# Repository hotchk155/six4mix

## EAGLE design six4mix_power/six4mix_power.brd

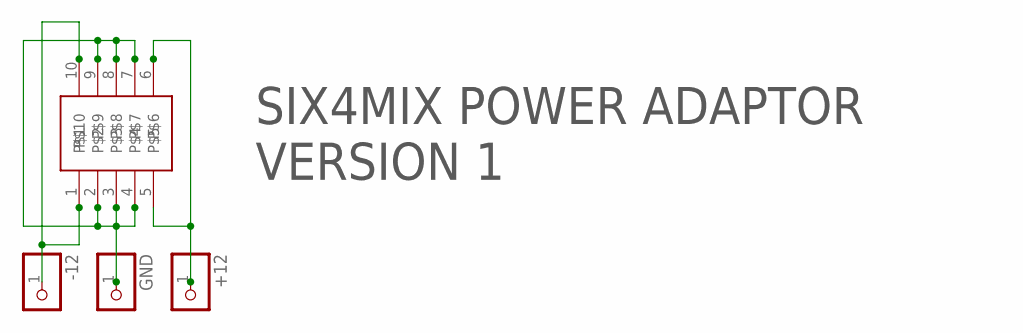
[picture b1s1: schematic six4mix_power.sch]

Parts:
+12: PINHD-1X1; 1X01
-12: PINHD-1X1; 1X01
GND: PINHD-1X1; 1X01
U$1: 2X5SMT

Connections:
GND: GND.1, U$1.2, U$1.3, U$1.4, U$1.7, U$1.8, U$1.9
unnamed: -12.1, U$1.1, U$1.10
unnamed: +12.1, U$1.5, U$1.6

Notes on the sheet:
SIX4MIX POWER ADAPTOR VERSION 1

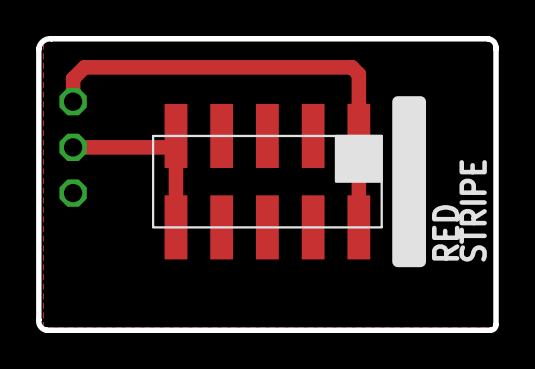
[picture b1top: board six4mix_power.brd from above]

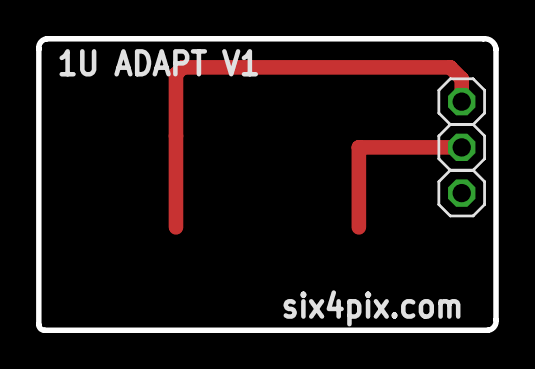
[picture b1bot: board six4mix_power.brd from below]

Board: 2 copper layers, 25.4 x 16.2 mm, 4 parts (3 on the bottom side), 3 nets.

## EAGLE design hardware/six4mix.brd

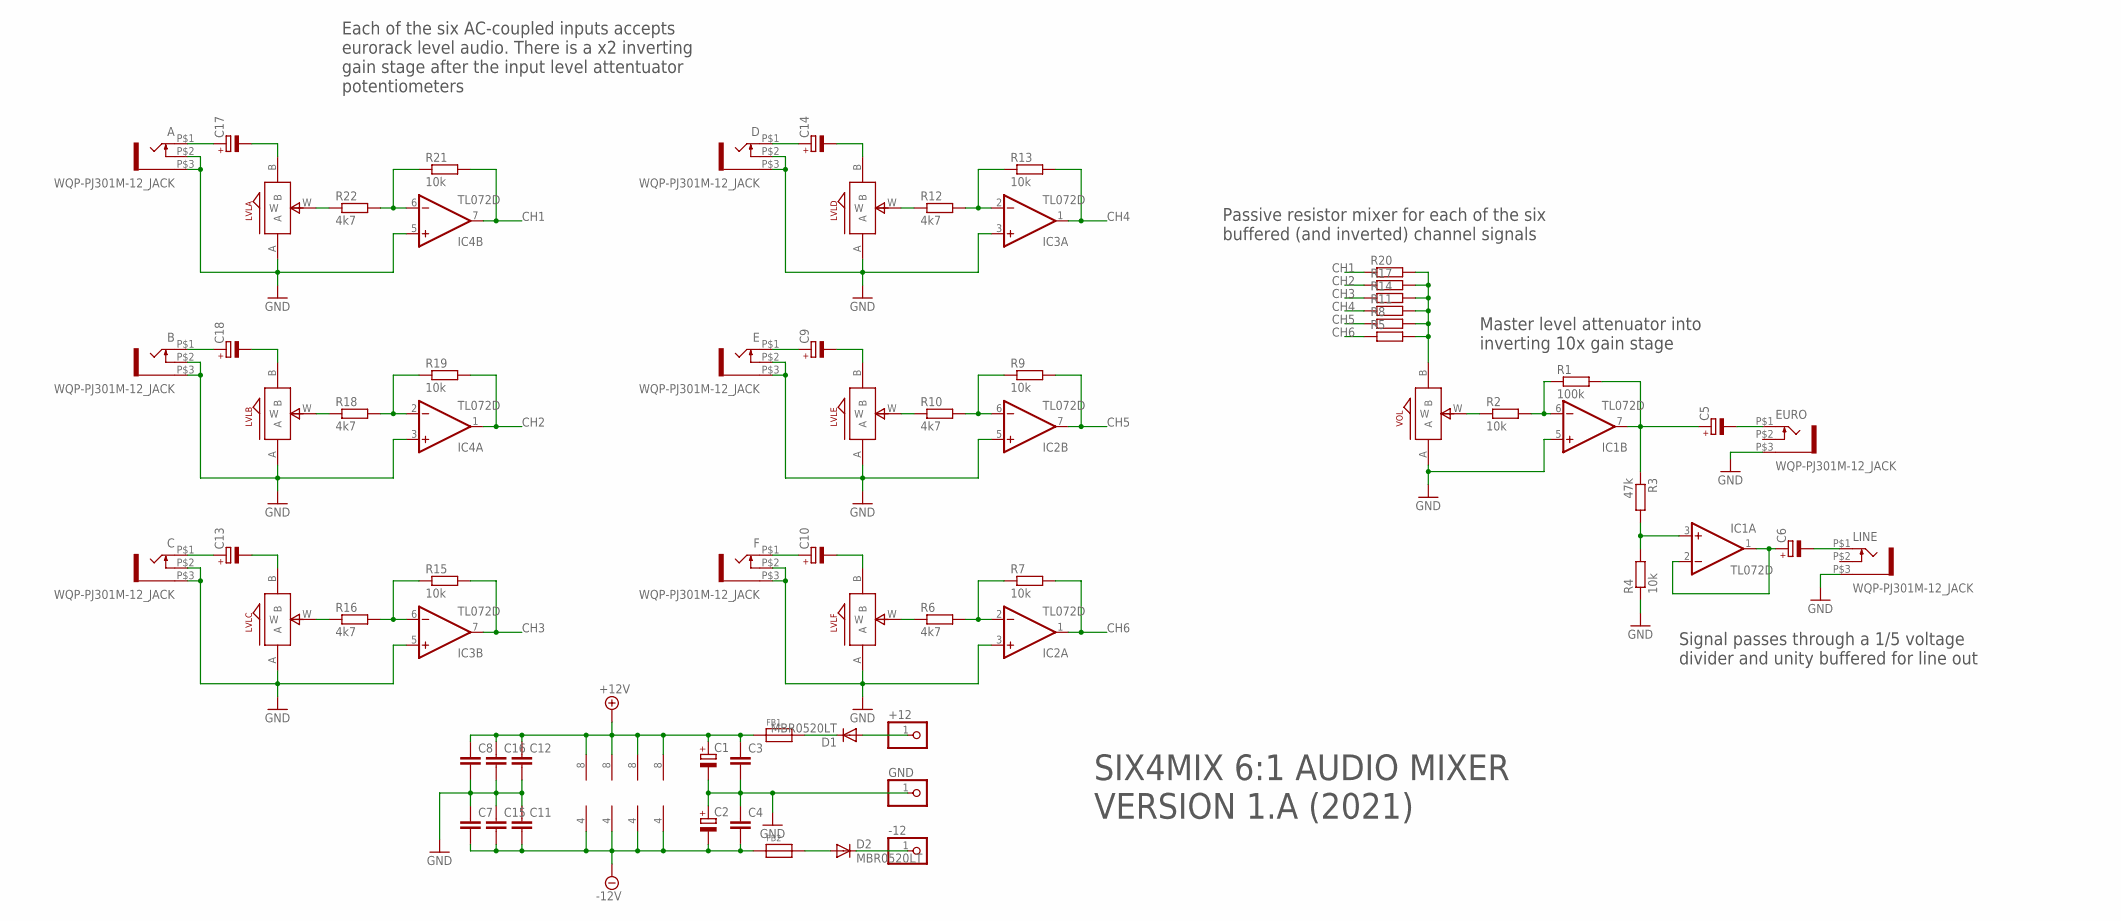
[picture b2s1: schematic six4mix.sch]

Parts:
+12: PINHD-1X1; 1X01
-12: PINHD-1X1; 1X01
A: WQP-PJ301M-12_JACK
B: WQP-PJ301M-12_JACK
C: WQP-PJ301M-12_JACK
C1, C2, C5, C6, C9, C10, C13, C14, C17, C18: CPOL-EUE2-4; E2-4
C3, C4, C7, C8, C11, C12, C15, C16: C-EUC0805; C0805
D: WQP-PJ301M-12_JACK
D1, D2: MBR0520LT; SOD123
E: WQP-PJ301M-12_JACK
EURO: WQP-PJ301M-12_JACK
F: WQP-PJ301M-12_JACK
FB1, FB2: FERRITE; 0603
GND: PINHD-1X1; 1X01
IC1, IC2, IC3, IC4: TL072D; SO08
LINE: WQP-PJ301M-12_JACK
LVLA: ALPS_POT_SMALL; SMALL_ALPS_POT
LVLB: ALPS_POT_SMALL; SMALL_ALPS_POT
LVLC: ALPS_POT_SMALL; SMALL_ALPS_POT
LVLD: ALPS_POT_SMALL; SMALL_ALPS_POT
LVLE: ALPS_POT_SMALL; SMALL_ALPS_POT
LVLF: ALPS_POT_SMALL; SMALL_ALPS_POT
R1: 100k; R0805
R2, R4, R7, R9, R13, R15, R19, R21: 10k; R0805
R3: 47k; R0805
R5, R8, R11, R14, R17, R20: R-EU_R0805; R0805
R6, R10, R12, R16, R18, R22: 4k7; R0805
VOL: ALPS_POT_SMALL; SMALL_ALPS_POT

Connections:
+12V: C1.+, C3.1, C8.1, C12.1, C16.1, FB1.1, IC1.8 (V+), IC2.8 (V+), IC3.8 (V+), IC4.8 (V+)
-12V: C2.-, C4.2, C7.2, C11.2, C15.2, FB2.1, IC1.4 (V-), IC2.4 (V-), IC3.4 (V-), IC4.4 (V-)
CH1: IC4.7 (OUT), R20.1, R21.2
CH2: IC4.1 (OUT), R17.1, R19.2
CH3: IC3.7 (OUT), R14.1, R15.2
CH4: IC3.1 (OUT), R11.1, R13.2
CH5: IC2.7 (OUT), R8.1, R9.2
CH6: IC2.1 (OUT), R5.1, R7.2
GND: A.P$2 (3), A.P$3 (1), B.P$2 (3), B.P$3 (1), C.P$2 (3), C.P$3 (1), C1.-, C2.+, C3.2, C4.1, C7.1, C8.2, C11.1, C12.2, C15.1, C16.2, D.P$2 (3), D.P$3 (1), E.P$2 (3), E.P$3 (1), EURO.P$3 (1), F.P$2 (3), F.P$3 (1), GND.1, IC1.5 (+IN), IC2.3 (+IN), IC2.5 (+IN), IC3.3 (+IN), IC3.5 (+IN), IC4.3 (+IN), IC4.5 (+IN), LINE.P$3 (1), LVLA.A, LVLB.A, LVLC.A, LVLD.A, LVLE.A, LVLF.A, R4.1, VOL.A
unnamed: C9.+, E.P$1 (2)
unnamed: C9.-, LVLE.B
unnamed: IC2.6 (-IN), R9.1, R10.2
unnamed: LVLE.W, R10.1
unnamed: C10.+, F.P$1 (2)
unnamed: C10.-, LVLF.B
unnamed: IC2.2 (-IN), R6.2, R7.1
unnamed: LVLF.W, R6.1
unnamed: C.P$1 (2), C13.+
unnamed: C13.-, LVLC.B
unnamed: IC3.6 (-IN), R15.1, R16.2
unnamed: LVLC.W, R16.1
unnamed: C14.+, D.P$1 (2)
unnamed: C14.-, LVLD.B
unnamed: IC3.2 (-IN), R12.2, R13.1
unnamed: LVLD.W, R12.1
unnamed: A.P$1 (2), C17.+
unnamed: C17.-, LVLA.B
unnamed: IC4.6 (-IN), R21.1, R22.2
unnamed: LVLA.W, R22.1
unnamed: B.P$1 (2), C18.+
unnamed: C18.-, LVLB.B
unnamed: IC4.2 (-IN), R18.2, R19.1
unnamed: LVLB.W, R18.1
unnamed: R5.2, R8.2, R11.2, R14.2, R17.2, R20.2, VOL.B
unnamed: C5.-, EURO.P$1 (2)
unnamed: C6.-, LINE.P$1 (2)
unnamed: R2.1, VOL.W
unnamed: IC1.6 (-IN), R1.1, R2.2
unnamed: C5.+, IC1.7 (OUT), R1.2, R3.1
unnamed: D1.C, FB1.2
unnamed: C6.+, IC1.1 (OUT), IC1.2 (-IN)
unnamed: IC1.3 (+IN), R3.2, R4.2
unnamed: +12.1, D1.A
unnamed: D2.A, FB2.2
unnamed: -12.1, D2.C

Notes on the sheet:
Each of the six AC-coupled inputs accepts eurorack level audio. There is a x2 inverting gain stage after the input level attentuator potentiometers
Passive resistor mixer for each of the six buffered (and inverted) channel signals
Master level attenuator into inverting 10x gain stage
Signal passes through a 1/5 voltage divider and unity buffered for line out
SIX4MIX 6:1 AUDIO MIXER VERSION 1.A (2021)

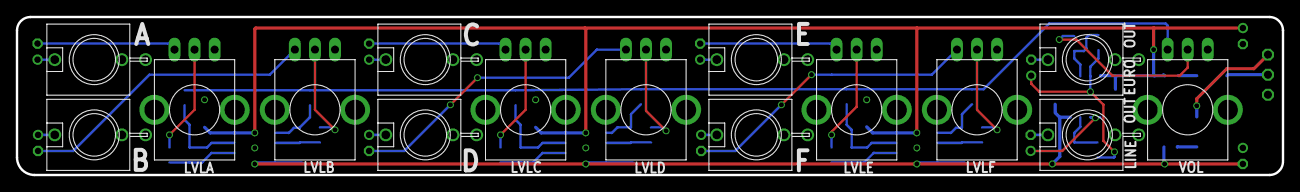
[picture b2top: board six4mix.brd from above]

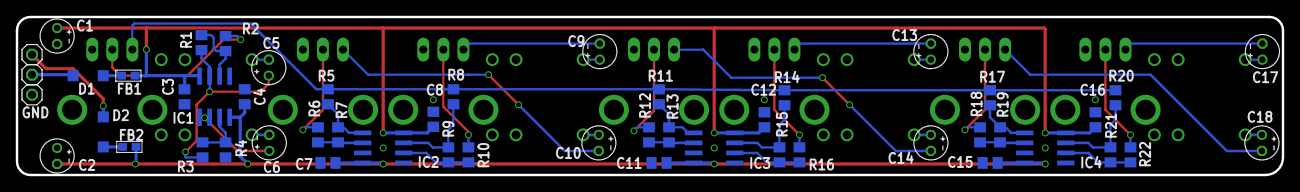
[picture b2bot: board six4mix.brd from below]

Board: 2 copper layers, 160.3 x 20.0 mm, 66 parts (51 on the bottom side), 45 nets.

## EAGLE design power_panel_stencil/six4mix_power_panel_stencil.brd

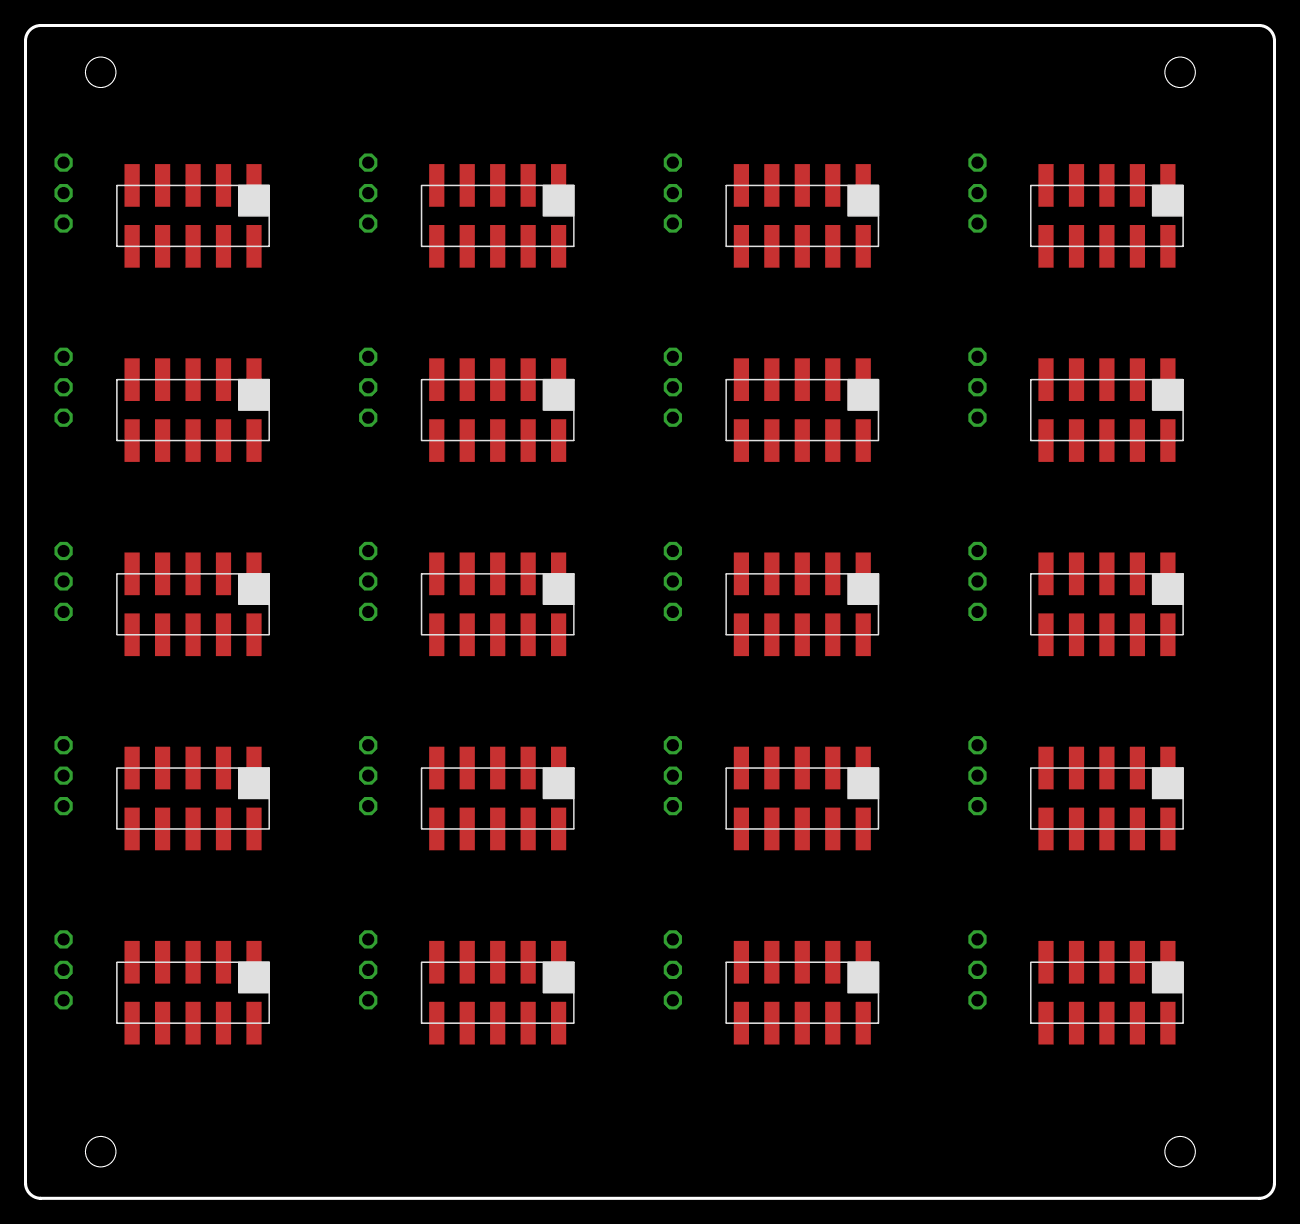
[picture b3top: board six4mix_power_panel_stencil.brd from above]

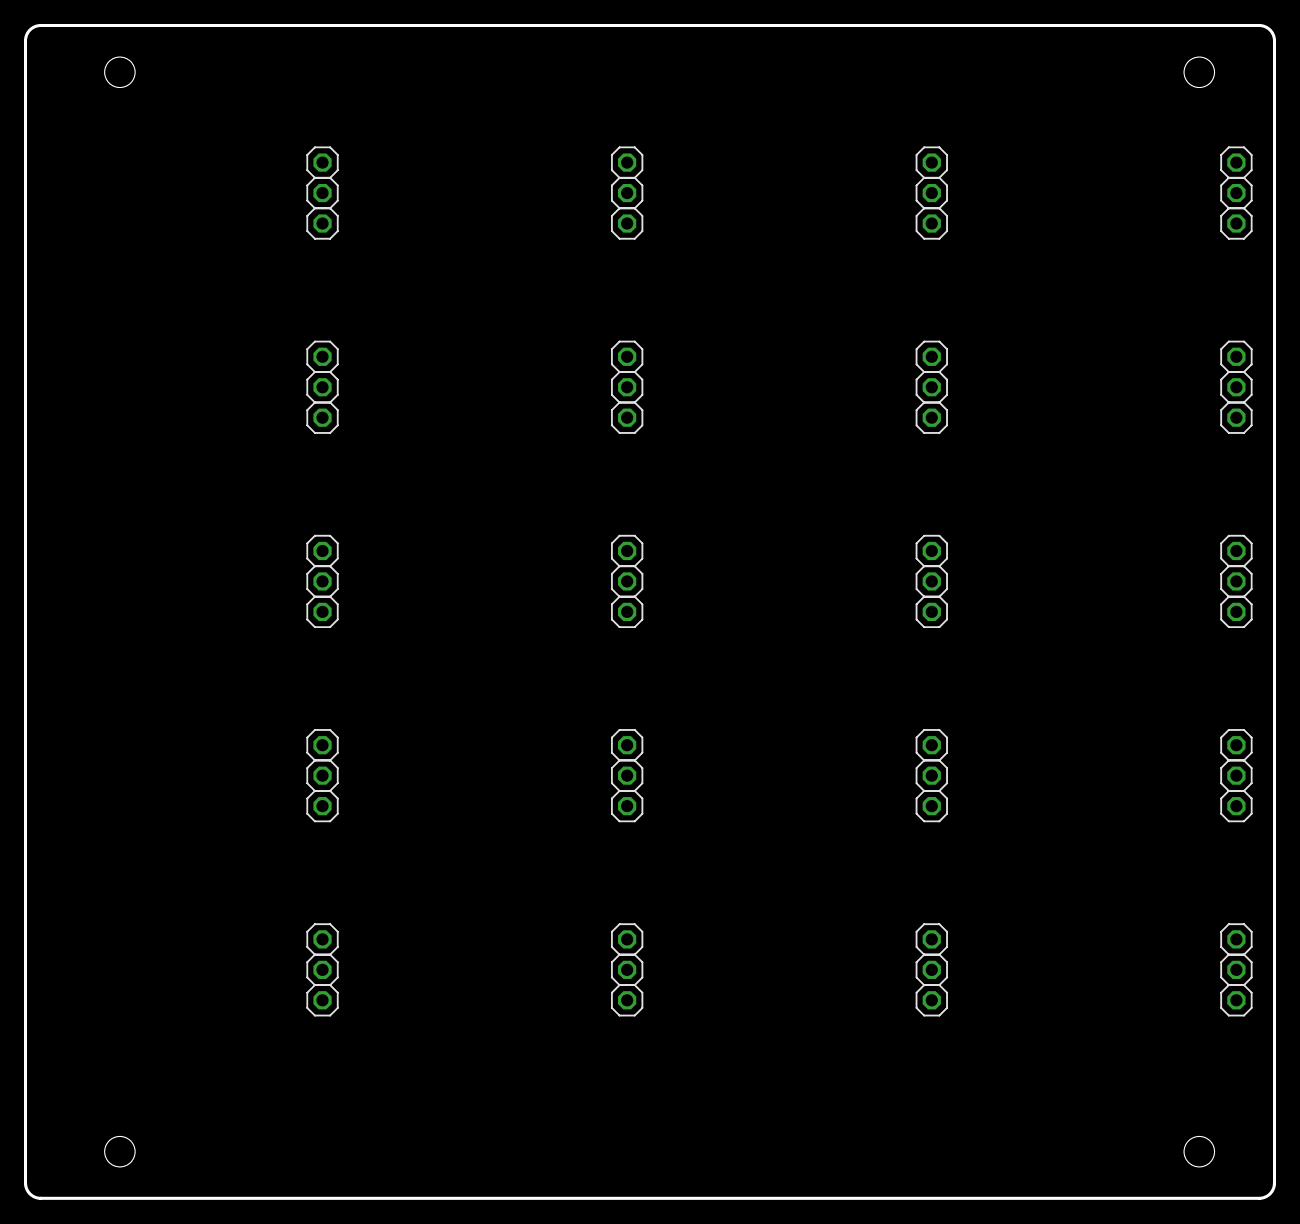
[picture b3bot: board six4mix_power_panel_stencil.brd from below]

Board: 2 copper layers, 104.1 x 97.8 mm, 80 parts (60 on the bottom side), 60 nets, no tracks yet.

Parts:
+1, +2, +3, +4, +5, +6, +7, +8, +9, +10, +11, +12, +13, +14, +15, +16, +17, +18, +19, +20: 1X01
-1, -2, -3, -4, -5, -6, -7, -8, -9, -10, -11, -12, -13, -14, -15, -16, -17, -18, -19, -20: 1X01
GND, GND1, GND2, GND3, GND4, GND5, GND6, GND7, GND8, GND9, GND10, GND11, GND12, GND13, GND14, GND15, GND16, GND17, GND18, GND19: 1X01
U$1, U$2, U$3, U$4, U$5, U$6, U$7, U$8, U$9, U$10, U$11, U$12, U$13, U$14, U$15, U$16, U$17, U$18, U$19, U$20: 2X5SMT

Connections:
GND: GND.1, U$1.2, U$1.3, U$1.4, U$1.7, U$1.8, U$1.9
GND1: GND1.1, U$2.2, U$2.3, U$2.4, U$2.7, U$2.8, U$2.9
GND2: GND2.1, U$3.2, U$3.3, U$3.4, U$3.7, U$3.8, U$3.9
GND3: GND3.1, U$4.2, U$4.3, U$4.4, U$4.7, U$4.8, U$4.9
GND4: GND4.1, U$5.2, U$5.3, U$5.4, U$5.7, U$5.8, U$5.9
GND5: GND5.1, U$6.2, U$6.3, U$6.4, U$6.7, U$6.8, U$6.9
GND6: GND6.1, U$7.2, U$7.3, U$7.4, U$7.7, U$7.8, U$7.9
GND7: GND7.1, U$8.2, U$8.3, U$8.4, U$8.7, U$8.8, U$8.9
GND8: GND8.1, U$9.2, U$9.3, U$9.4, U$9.7, U$9.8, U$9.9
GND9: GND9.1, U$10.2, U$10.3, U$10.4, U$10.7, U$10.8, U$10.9
GND10: GND10.1, U$11.2, U$11.3, U$11.4, U$11.7, U$11.8, U$11.9
GND11: GND11.1, U$12.2, U$12.3, U$12.4, U$12.7, U$12.8, U$12.9
GND12: GND12.1, U$13.2, U$13.3, U$13.4, U$13.7, U$13.8, U$13.9
GND13: GND13.1, U$14.2, U$14.3, U$14.4, U$14.7, U$14.8, U$14.9
GND14: GND14.1, U$15.2, U$15.3, U$15.4, U$15.7, U$15.8, U$15.9
GND15: GND15.1, U$16.2, U$16.3, U$16.4, U$16.7, U$16.8, U$16.9
GND16: GND16.1, U$17.2, U$17.3, U$17.4, U$17.7, U$17.8, U$17.9
GND17: GND17.1, U$18.2, U$18.3, U$18.4, U$18.7, U$18.8, U$18.9
GND18: GND18.1, U$19.2, U$19.3, U$19.4, U$19.7, U$19.8, U$19.9
GND19: GND19.1, U$20.2, U$20.3, U$20.4, U$20.7, U$20.8, U$20.9
unnamed: -12.1, U$1.1, U$1.10
unnamed: +12.1, U$1.5, U$1.6
unnamed: -1.1, U$2.1, U$2.10
unnamed: +1.1, U$2.5, U$2.6
unnamed: -2.1, U$3.1, U$3.10
unnamed: +2.1, U$3.5, U$3.6
unnamed: -3.1, U$4.1, U$4.10
unnamed: +3.1, U$4.5, U$4.6
unnamed: -4.1, U$5.1, U$5.10
unnamed: +4.1, U$5.5, U$5.6
unnamed: -5.1, U$6.1, U$6.10
unnamed: +5.1, U$6.5, U$6.6
unnamed: -6.1, U$7.1, U$7.10
unnamed: +6.1, U$7.5, U$7.6
unnamed: -7.1, U$8.1, U$8.10
unnamed: +7.1, U$8.5, U$8.6
unnamed: -8.1, U$9.1, U$9.10
unnamed: +8.1, U$9.5, U$9.6
unnamed: -9.1, U$10.1, U$10.10
unnamed: +9.1, U$10.5, U$10.6
unnamed: -10.1, U$11.1, U$11.10
unnamed: +10.1, U$11.5, U$11.6
unnamed: -11.1, U$12.1, U$12.10
unnamed: +11.1, U$12.5, U$12.6
unnamed: -13.1, U$13.1, U$13.10
unnamed: +13.1, U$13.5, U$13.6
unnamed: -14.1, U$14.1, U$14.10
unnamed: +14.1, U$14.5, U$14.6
unnamed: -15.1, U$15.1, U$15.10
unnamed: +15.1, U$15.5, U$15.6
unnamed: -16.1, U$16.1, U$16.10
unnamed: +16.1, U$16.5, U$16.6
unnamed: -17.1, U$17.1, U$17.10
unnamed: +17.1, U$17.5, U$17.6
unnamed: -18.1, U$18.1, U$18.10
unnamed: +18.1, U$18.5, U$18.6
unnamed: -19.1, U$19.1, U$19.10
unnamed: +19.1, U$19.5, U$19.6
unnamed: -20.1, U$20.1, U$20.10
unnamed: +20.1, U$20.5, U$20.6

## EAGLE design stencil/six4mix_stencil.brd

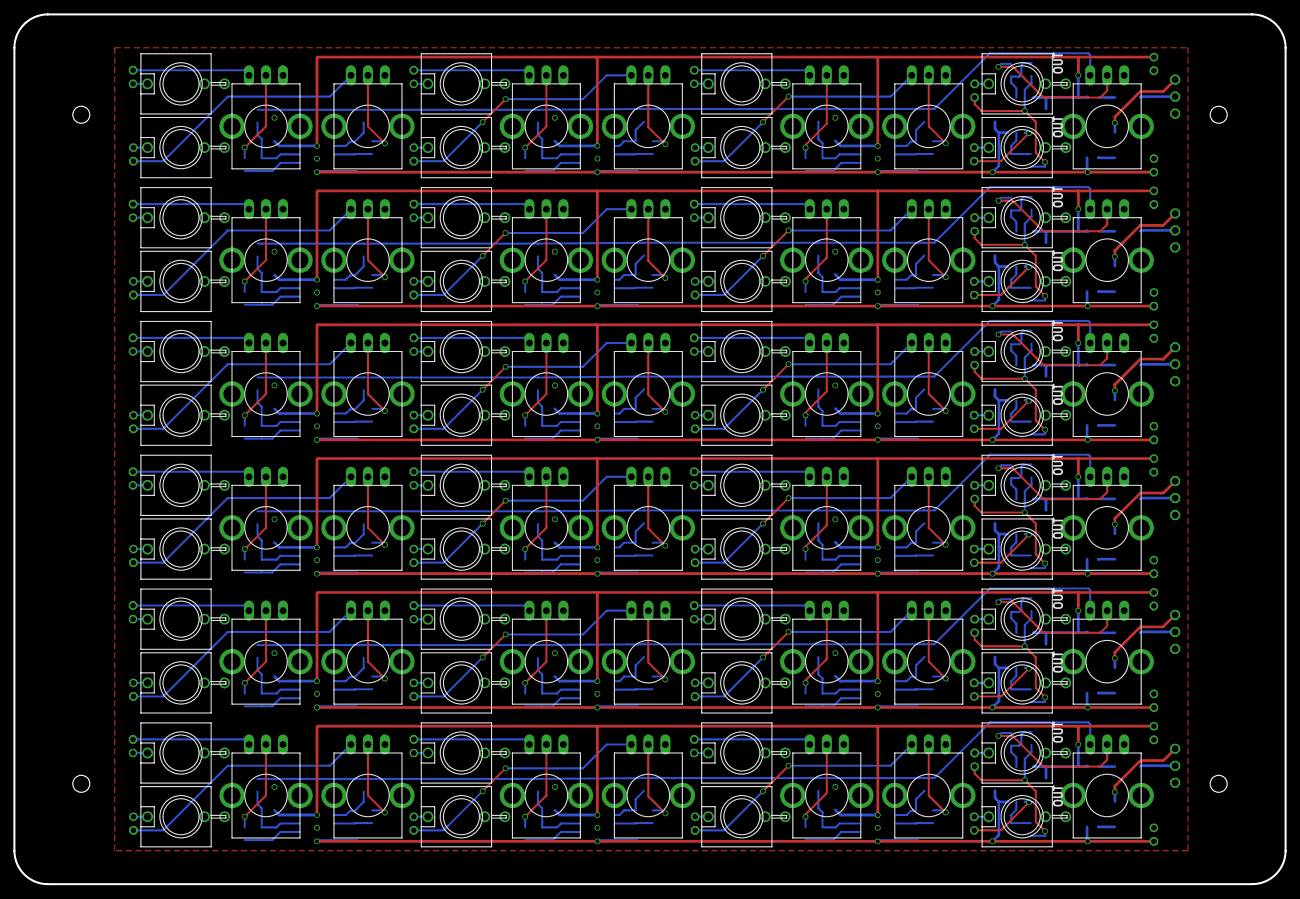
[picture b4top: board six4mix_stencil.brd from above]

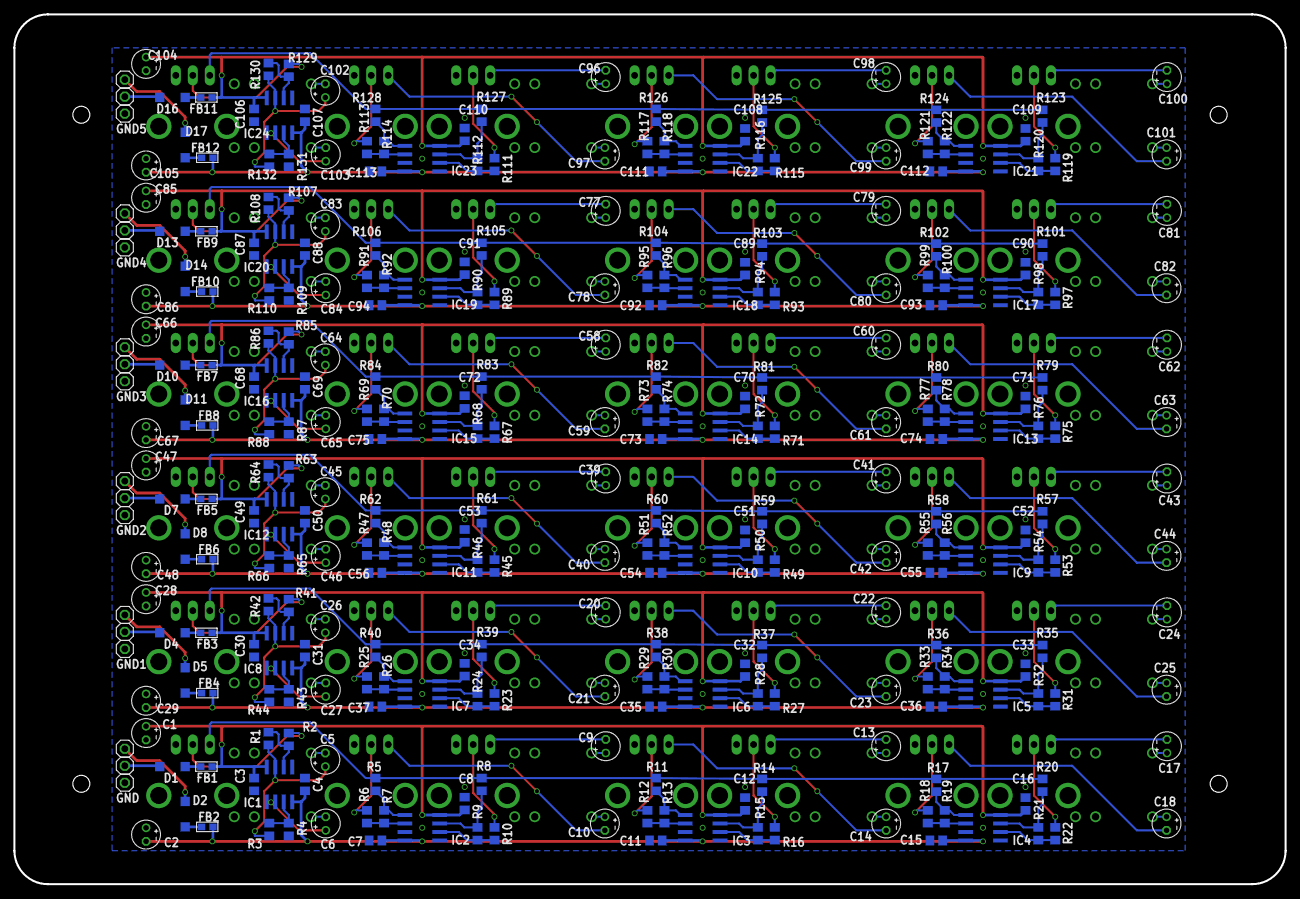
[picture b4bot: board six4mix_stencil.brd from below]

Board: 2 copper layers, 190.0 x 130.0 mm, 396 parts (306 on the bottom side), 265 nets.

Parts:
+1, +2, +3, +4, +5, +12: 1X01
-1, -2, -3, -4, -5, -12: 1X01
A, A1, A2, A3, A4, A5: WQP-PJ301M-12_JACK
B, B1, B2, B3, B4, B5: WQP-PJ301M-12_JACK
C, C19, C38, C57, C76, C95: WQP-PJ301M-12_JACK
C1, C2, C5, C6, C9, C10, C13, C14, C17, C18, C20, C21, C22, C23, C24, C25, C26, C27, C28, C29, C39, C40, C41, C42, C43, C44, C45, C46, C47, C48, C58, C59, C60, C61, C62, C63, C64, C65, C66, C67, C77, C78, C79, C80, C81, C82, C83, C84, C85, C86, C96, C97, C98, C99, C100, C101, C102, C103, C104, C105: E2-4
C3, C4, C7, C8, C11, C12, C15, C16, C30, C31, C32, C33, C34, C35, C36, C37, C49, C50, C51, C52, C53, C54, C55, C56, C68, C69, C70, C71, C72, C73, C74, C75, C87, C88, C89, C90, C91, C92, C93, C94, C106, C107, C108, C109, C110, C111, C112, C113: C0805
D, D3, D6, D9, D12, D15: WQP-PJ301M-12_JACK
D1, D2, D4, D5, D7, D8, D10, D11, D13, D14, D16, D17: MBR0520LT; SOD123
E, E1, E2, E3, E4, E5: WQP-PJ301M-12_JACK
EURO, EURO1, EURO2, EURO3, EURO4, EURO5: WQP-PJ301M-12_JACK
F, F1, F2, F3, F4, F5: WQP-PJ301M-12_JACK
FB1, FB2, FB3, FB4, FB5, FB6, FB7, FB8, FB9, FB10, FB11, FB12: 0603
GND, GND1, GND2, GND3, GND4, GND5: 1X01
IC1, IC2, IC3, IC4, IC5, IC6, IC7, IC8, IC9, IC10, IC11, IC12, IC13, IC14, IC15, IC16, IC17, IC18, IC19, IC20, IC21, IC22, IC23, IC24: TL072D; SO08
LINE, LINE1, LINE2, LINE3, LINE4, LINE5: WQP-PJ301M-12_JACK
LVLA, LVLA1, LVLA2, LVLA3, LVLA4, LVLA5: ALPS_POT_SMALL; SMALL_ALPS_POT
LVLB, LVLB1, LVLB2, LVLB3, LVLB4, LVLB5: ALPS_POT_SMALL; SMALL_ALPS_POT
LVLC, LVLC1, LVLC2, LVLC3, LVLC4, LVLC5: ALPS_POT_SMALL; SMALL_ALPS_POT
LVLD, LVLD1, LVLD2, LVLD3, LVLD4, LVLD5: ALPS_POT_SMALL; SMALL_ALPS_POT
LVLE, LVLE1, LVLE2, LVLE3, LVLE4, LVLE5: ALPS_POT_SMALL; SMALL_ALPS_POT
LVLF, LVLF1, LVLF2, LVLF3, LVLF4, LVLF5: ALPS_POT_SMALL; SMALL_ALPS_POT
R1, R42, R64, R86, R108, R130: 100k; R0805
R2, R4, R7, R9, R13, R15, R19, R21, R24, R26, R28, R30, R32, R34, R41, R43, R46, R48, R50, R52, R54, R56, R63, R65, R68, R70, R72, R74, R76, R78, R85, R87, R90, R92, R94, R96, R98, R100, R107, R109, R112, R114, R116, R118, R120, R122, R129, R131: 10k; R0805
R3, R44, R66, R88, R110, R132: 47k; R0805
R5, R8, R11, R14, R17, R20, R35, R36, R37, R38, R39, R40, R57, R58, R59, R60, R61, R62, R79, R80, R81, R82, R83, R84, R101, R102, R103, R104, R105, R106, R123, R124, R125, R126, R127, R128: R0805
R6, R10, R12, R16, R18, R22, R23, R25, R27, R29, R31, R33, R45, R47, R49, R51, R53, R55, R67, R69, R71, R73, R75, R77, R89, R91, R93, R95, R97, R99, R111, R113, R115, R117, R119, R121: 4k7; R0805
VOL, VOL1, VOL2, VOL3, VOL4, VOL5: ALPS_POT_SMALL; SMALL_ALPS_POT

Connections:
+12V: C1.+, C3.1, C8.1, C12.1, C16.1, FB1.1, IC1.8, IC2.8, IC3.8, IC4.8
+12V1: C28.+, C30.1, C32.1, C33.1, C34.1, FB3.1, IC5.8, IC6.8, IC7.8, IC8.8
+12V2: C47.+, C49.1, C51.1, C52.1, C53.1, FB5.1, IC9.8, IC10.8, IC11.8, IC12.8
+12V3: C66.+, C68.1, C70.1, C71.1, C72.1, FB7.1, IC13.8, IC14.8, IC15.8, IC16.8
+12V4: C85.+, C87.1, C89.1, C90.1, C91.1, FB9.1, IC17.8, IC18.8, IC19.8, IC20.8
+12V5: C104.+, C106.1, C108.1, C109.1, C110.1, FB11.1, IC21.8, IC22.8, IC23.8, IC24.8
-12V: C2.-, C4.2, C7.2, C11.2, C15.2, FB2.1, IC1.4, IC2.4, IC3.4, IC4.4
-12V1: C29.-, C31.2, C35.2, C36.2, C37.2, FB4.1, IC5.4, IC6.4, IC7.4, IC8.4
-12V2: C48.-, C50.2, C54.2, C55.2, C56.2, FB6.1, IC9.4, IC10.4, IC11.4, IC12.4
-12V3: C67.-, C69.2, C73.2, C74.2, C75.2, FB8.1, IC13.4, IC14.4, IC15.4, IC16.4
-12V4: C86.-, C88.2, C92.2, C93.2, C94.2, FB10.1, IC17.4, IC18.4, IC19.4, IC20.4
-12V5: C105.-, C107.2, C111.2, C112.2, C113.2, FB12.1, IC21.4, IC22.4, IC23.4, IC24.4
CH1: IC4.7, R20.1, R21.2
CH2: IC4.1, R17.1, R19.2
CH3: IC3.7, R14.1, R15.2
CH4: IC3.1, R11.1, R13.2
CH5: IC2.7, R8.1, R9.2
CH6: IC2.1, R5.1, R7.2
CH7: IC5.7, R32.2, R35.1
CH8: IC5.1, R34.2, R36.1
CH9: IC6.7, R28.2, R37.1
CH10: IC6.1, R30.2, R38.1
CH11: IC7.7, R24.2, R39.1
CH12: IC7.1, R26.2, R40.1
CH13: IC9.7, R54.2, R57.1
CH14: IC9.1, R56.2, R58.1
CH15: IC10.7, R50.2, R59.1
CH16: IC10.1, R52.2, R60.1
CH17: IC11.7, R46.2, R61.1
CH18: IC11.1, R48.2, R62.1
CH19: IC13.7, R76.2, R79.1
CH20: IC13.1, R78.2, R80.1
CH21: IC14.7, R72.2, R81.1
CH22: IC14.1, R74.2, R82.1
CH23: IC15.7, R68.2, R83.1
CH24: IC15.1, R70.2, R84.1
CH25: IC17.7, R98.2, R101.1
CH26: IC17.1, R100.2, R102.1
CH27: IC18.7, R94.2, R103.1
CH28: IC18.1, R96.2, R104.1
CH29: IC19.7, R90.2, R105.1
CH30: IC19.1, R92.2, R106.1
CH31: IC21.7, R120.2, R123.1
CH32: IC21.1, R122.2, R124.1
CH33: IC22.7, R116.2, R125.1
CH34: IC22.1, R118.2, R126.1
CH35: IC23.7, R112.2, R127.1
CH36: IC23.1, R114.2, R128.1
GND: A.P$2, A.P$3, A1.P$2, A1.P$3, A2.P$2, A2.P$3, A3.P$2, A3.P$3, A4.P$2, A4.P$3, A5.P$2, A5.P$3, B.P$2, B.P$3, B1.P$2, B1.P$3, B2.P$2, B2.P$3, B3.P$2, B3.P$3, B4.P$2, B4.P$3, B5.P$2, B5.P$3, C.P$2, C.P$3, C1.-, C2.+, C3.2, C4.1, C7.1, C8.2, C11.1, C12.2, C15.1, C16.2, C19.P$2, C19.P$3, C28.-, C29.+, C30.2, C31.1, C32.2, C33.2, C34.2, C35.1, C36.1, C37.1, C38.P$2, C38.P$3, C47.-, C48.+, C49.2, C50.1, C51.2, C52.2, C53.2, C54.1, C55.1, C56.1, C57.P$2, C57.P$3, C66.-, C67.+, C68.2, C69.1, C70.2, C71.2, C72.2, C73.1, C74.1, C75.1, C76.P$2, C76.P$3, C85.-, C86.+, C87.2, C88.1, C89.2, C90.2, C91.2, C92.1, C93.1, C94.1, C95.P$2, C95.P$3, C104.-, C105.+, C106.2, C107.1, C108.2, C109.2, C110.2, C111.1, C112.1, C113.1, D.P$2, D.P$3, D3.P$2, D3.P$3, D6.P$2, D6.P$3, D9.P$2, D9.P$3, D12.P$2, D12.P$3, D15.P$2, D15.P$3, E.P$2, E.P$3, E1.P$2, E1.P$3, E2.P$2, E2.P$3, E3.P$2, E3.P$3, E4.P$2, E4.P$3, E5.P$2, E5.P$3, EURO.P$3, EURO1.P$3, EURO2.P$3, EURO3.P$3, EURO4.P$3, EURO5.P$3, F.P$2, F.P$3, F1.P$2, F1.P$3, F2.P$2, F2.P$3, F3.P$2, F3.P$3, F4.P$2, F4.P$3, F5.P$2, F5.P$3, GND.1, GND1.1, GND2.1, GND3.1, GND4.1, GND5.1, IC1.5, IC2.3, IC2.5, IC3.3, IC3.5, IC4.3, IC4.5, IC5.3, IC5.5, IC6.3, IC6.5, IC7.3, IC7.5, IC8.5, IC9.3, IC9.5, IC10.3, IC10.5, IC11.3, IC11.5, IC12.5, IC13.3, IC13.5, IC14.3, IC14.5, IC15.3, IC15.5, IC16.5, IC17.3, IC17.5, IC18.3, IC18.5, IC19.3, IC19.5, IC20.5, IC21.3, IC21.5, IC22.3, IC22.5, IC23.3, IC23.5, IC24.5, LINE.P$3, LINE1.P$3, LINE2.P$3, LINE3.P$3, LINE4.P$3, LINE5.P$3, LVLA.A, LVLA1.A, LVLA2.A, LVLA3.A, LVLA4.A, LVLA5.A, LVLB.A, LVLB1.A, LVLB2.A, LVLB3.A, LVLB4.A, LVLB5.A, LVLC.A, LVLC1.A, LVLC2.A, LVLC3.A, LVLC4.A, LVLC5.A, LVLD.A, LVLD1.A, LVLD2.A, LVLD3.A, LVLD4.A, LVLD5.A, LVLE.A, LVLE1.A, LVLE2.A, LVLE3.A, LVLE4.A, LVLE5.A, LVLF.A, LVLF1.A, LVLF2.A, LVLF3.A, LVLF4.A, LVLF5.A, R4.1, R43.1, R65.1, R87.1, R109.1, R131.1, VOL.A, VOL1.A, VOL2.A, VOL3.A, VOL4.A, VOL5.A
unnamed: C9.+, E.P$1
unnamed: C9.-, LVLE.B
unnamed: IC2.6, R9.1, R10.2
unnamed: LVLE.W, R10.1
unnamed: C10.+, F.P$1
unnamed: C10.-, LVLF.B
unnamed: IC2.2, R6.2, R7.1
unnamed: LVLF.W, R6.1
unnamed: C.P$1, C13.+
unnamed: C13.-, LVLC.B
unnamed: IC3.6, R15.1, R16.2
unnamed: LVLC.W, R16.1
unnamed: C14.+, D.P$1
unnamed: C14.-, LVLD.B
unnamed: IC3.2, R12.2, R13.1
unnamed: LVLD.W, R12.1
unnamed: A.P$1, C17.+
unnamed: C17.-, LVLA.B
unnamed: IC4.6, R21.1, R22.2
unnamed: LVLA.W, R22.1
unnamed: B.P$1, C18.+
unnamed: C18.-, LVLB.B
unnamed: IC4.2, R18.2, R19.1
unnamed: LVLB.W, R18.1
unnamed: R5.2, R8.2, R11.2, R14.2, R17.2, R20.2, VOL.B
unnamed: C5.-, EURO.P$1
unnamed: C6.-, LINE.P$1
unnamed: R2.1, VOL.W
unnamed: IC1.6, R1.1, R2.2
unnamed: C5.+, IC1.7, R1.2, R3.1
unnamed: D1.C, FB1.2
unnamed: C6.+, IC1.1, IC1.2
unnamed: IC1.3, R3.2, R4.2
unnamed: +12.1, D1.A
unnamed: D2.A, FB2.2
unnamed: -12.1, D2.C
unnamed: C20.-, LVLE1.B
unnamed: IC7.6, R23.2, R24.1
unnamed: C21.+, F1.P$1
unnamed: C21.-, LVLF1.B
unnamed: IC7.2, R25.2, R26.1
unnamed: LVLF1.W, R25.1
unnamed: C19.P$1, C22.+
unnamed: C22.-, LVLC1.B
unnamed: IC6.6, R27.2, R28.1
unnamed: LVLC1.W, R27.1
unnamed: C23.+, D3.P$1
unnamed: C23.-, LVLD1.B
unnamed: IC6.2, R29.2, R30.1
unnamed: LVLD1.W, R29.1
unnamed: A1.P$1, C24.+
unnamed: C24.-, LVLA1.B
unnamed: IC5.6, R31.2, R32.1
unnamed: LVLA1.W, R31.1
unnamed: B1.P$1, C25.+
unnamed: C25.-, LVLB1.B
unnamed: IC5.2, R33.2, R34.1
unnamed: LVLB1.W, R33.1
unnamed: LVLE1.W, R23.1
unnamed: C20.+, E1.P$1
unnamed: R35.2, R36.2, R37.2, R38.2, R39.2, R40.2, VOL1.B
unnamed: R41.1, VOL1.W
unnamed: IC8.6, R41.2, R42.1
unnamed: C26.+, IC8.7, R42.2, R44.1
unnamed: C26.-, EURO1.P$1
unnamed: C27.-, LINE1.P$1
unnamed: C27.+, IC8.1, IC8.2
unnamed: IC8.3, R43.2, R44.2
unnamed: D4.C, FB3.2
unnamed: +1.1, D4.A
unnamed: D5.A, FB4.2
unnamed: -1.1, D5.C
unnamed: C39.-, LVLE2.B
unnamed: IC11.6, R45.2, R46.1
unnamed: C40.+, F2.P$1
unnamed: C40.-, LVLF2.B
unnamed: IC11.2, R47.2, R48.1
unnamed: LVLF2.W, R47.1
unnamed: C38.P$1, C41.+
unnamed: C41.-, LVLC2.B
unnamed: IC10.6, R49.2, R50.1
unnamed: LVLC2.W, R49.1
unnamed: C42.+, D6.P$1
unnamed: C42.-, LVLD2.B
unnamed: IC10.2, R51.2, R52.1
unnamed: LVLD2.W, R51.1
unnamed: A2.P$1, C43.+
unnamed: C43.-, LVLA2.B
unnamed: IC9.6, R53.2, R54.1
unnamed: LVLA2.W, R53.1
unnamed: B2.P$1, C44.+
unnamed: C44.-, LVLB2.B
unnamed: IC9.2, R55.2, R56.1
unnamed: LVLB2.W, R55.1
unnamed: LVLE2.W, R45.1
unnamed: C39.+, E2.P$1
unnamed: R57.2, R58.2, R59.2, R60.2, R61.2, R62.2, VOL2.B
unnamed: R63.1, VOL2.W
unnamed: IC12.6, R63.2, R64.1
unnamed: C45.+, IC12.7, R64.2, R66.1
unnamed: C45.-, EURO2.P$1
unnamed: C46.-, LINE2.P$1
unnamed: C46.+, IC12.1, IC12.2
unnamed: IC12.3, R65.2, R66.2
unnamed: D7.C, FB5.2
unnamed: +2.1, D7.A
unnamed: D8.A, FB6.2
unnamed: -2.1, D8.C
unnamed: C58.-, LVLE3.B
unnamed: IC15.6, R67.2, R68.1
unnamed: C59.+, F3.P$1
unnamed: C59.-, LVLF3.B
unnamed: IC15.2, R69.2, R70.1
unnamed: LVLF3.W, R69.1
unnamed: C57.P$1, C60.+
unnamed: C60.-, LVLC3.B
unnamed: IC14.6, R71.2, R72.1
unnamed: LVLC3.W, R71.1
unnamed: C61.+, D9.P$1
unnamed: C61.-, LVLD3.B
unnamed: IC14.2, R73.2, R74.1
unnamed: LVLD3.W, R73.1
unnamed: A3.P$1, C62.+
unnamed: C62.-, LVLA3.B
unnamed: IC13.6, R75.2, R76.1
unnamed: LVLA3.W, R75.1
unnamed: B3.P$1, C63.+
unnamed: C63.-, LVLB3.B
unnamed: IC13.2, R77.2, R78.1
unnamed: LVLB3.W, R77.1
unnamed: LVLE3.W, R67.1
unnamed: C58.+, E3.P$1
unnamed: R79.2, R80.2, R81.2, R82.2, R83.2, R84.2, VOL3.B
unnamed: R85.1, VOL3.W
unnamed: IC16.6, R85.2, R86.1
unnamed: C64.+, IC16.7, R86.2, R88.1
unnamed: C64.-, EURO3.P$1
unnamed: C65.-, LINE3.P$1
unnamed: C65.+, IC16.1, IC16.2
unnamed: IC16.3, R87.2, R88.2
unnamed: D10.C, FB7.2
unnamed: +3.1, D10.A
unnamed: D11.A, FB8.2
unnamed: -3.1, D11.C
unnamed: C77.-, LVLE4.B
unnamed: IC19.6, R89.2, R90.1
unnamed: C78.+, F4.P$1
unnamed: C78.-, LVLF4.B
unnamed: IC19.2, R91.2, R92.1
unnamed: LVLF4.W, R91.1
unnamed: C76.P$1, C79.+
unnamed: C79.-, LVLC4.B
unnamed: IC18.6, R93.2, R94.1
unnamed: LVLC4.W, R93.1
unnamed: C80.+, D12.P$1
unnamed: C80.-, LVLD4.B
unnamed: IC18.2, R95.2, R96.1
unnamed: LVLD4.W, R95.1
unnamed: A4.P$1, C81.+
unnamed: C81.-, LVLA4.B
unnamed: IC17.6, R97.2, R98.1
unnamed: LVLA4.W, R97.1
unnamed: B4.P$1, C82.+
unnamed: C82.-, LVLB4.B
unnamed: IC17.2, R99.2, R100.1
unnamed: LVLB4.W, R99.1
unnamed: LVLE4.W, R89.1
unnamed: C77.+, E4.P$1
unnamed: R101.2, R102.2, R103.2, R104.2, R105.2, R106.2, VOL4.B
unnamed: R107.1, VOL4.W
unnamed: IC20.6, R107.2, R108.1
unnamed: C83.+, IC20.7, R108.2, R110.1
unnamed: C83.-, EURO4.P$1
unnamed: C84.-, LINE4.P$1
unnamed: C84.+, IC20.1, IC20.2
unnamed: IC20.3, R109.2, R110.2
unnamed: D13.C, FB9.2
unnamed: +4.1, D13.A
unnamed: D14.A, FB10.2
unnamed: -4.1, D14.C
unnamed: C96.-, LVLE5.B
unnamed: IC23.6, R111.2, R112.1
unnamed: C97.+, F5.P$1
unnamed: C97.-, LVLF5.B
unnamed: IC23.2, R113.2, R114.1
unnamed: LVLF5.W, R113.1
unnamed: C95.P$1, C98.+
unnamed: C98.-, LVLC5.B
unnamed: IC22.6, R115.2, R116.1
unnamed: LVLC5.W, R115.1
unnamed: C99.+, D15.P$1
unnamed: C99.-, LVLD5.B
unnamed: IC22.2, R117.2, R118.1
unnamed: LVLD5.W, R117.1
unnamed: A5.P$1, C100.+
unnamed: C100.-, LVLA5.B
unnamed: IC21.6, R119.2, R120.1
unnamed: LVLA5.W, R119.1
unnamed: B5.P$1, C101.+
unnamed: C101.-, LVLB5.B
unnamed: IC21.2, R121.2, R122.1
unnamed: LVLB5.W, R121.1
unnamed: LVLE5.W, R111.1
unnamed: C96.+, E5.P$1
unnamed: R123.2, R124.2, R125.2, R126.2, R127.2, R128.2, VOL5.B
unnamed: R129.1, VOL5.W
unnamed: IC24.6, R129.2, R130.1
unnamed: C102.+, IC24.7, R130.2, R132.1
unnamed: C102.-, EURO5.P$1
unnamed: C103.-, LINE5.P$1
unnamed: C103.+, IC24.1, IC24.2
unnamed: IC24.3, R131.2, R132.2
unnamed: D16.C, FB11.2
unnamed: +5.1, D16.A
unnamed: D17.A, FB12.2
unnamed: -5.1, D17.C

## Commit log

2021-04-12 1vpcb
2021-07-17 values
2022-05-24 front panel
2022-08-08 reorg
2022-08-08 rename
2022-08-08 id inputs A-F
2022-08-08 socket labels to docu layer
2022-08-08 stencil
2022-11-22 power board
2023-12-18 6.5mm holes
2023-12-18 updates v3 larger holes
